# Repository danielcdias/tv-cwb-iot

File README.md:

# tv-cwb-iot

Projeto de pesquisa **Terraço Verde Curitiba IoT**. Rede de sensores criada para monitorar protótipo de telhado verde, efetuando comparação entre tipo de cobertura intensiva e extensiva. Coleta de dados sobre temperatura do solo, quantidade de chuva, atraso de pico e água absorvida.

Este projeto implementa o firmware dos microcontroladores ligados aos sensores, o border router que liga a rede de sensores à internet, e do servidor de aplicação que recebe dos dados coletados, os trata e dispobibiliza através de aplicação web e móvel.

As pastas do projeto estão organizadas da seguinte forma:
- *contiki*: sistema operacional contiki, contendo o código para criação do firmware dos microcontroladores responsáveis pela leitura dos sensores.
- *docker*: configuração para executar o servidor de aplicação (Django/Python) e o banco de dados (MariaDB) em um docker composer.
- *forwarder*: aplicação em Python responsável por receber os dados dos microcontroladores e encaminhá-los ao servidor de aplicação.
- *mobile*: aplicação móvel desenvolvida em Google Flutter para apresentar os dados lidos dos sensores (ainda não implementado).
- *pcb*: projeto de placas impressas utilizadas no projeto.
- *server*: servidor de aplicação desenvolvido em Django/Python, responsável por receber, tratar, armazenar e apresentar os dados lidos pela rede de sensores.

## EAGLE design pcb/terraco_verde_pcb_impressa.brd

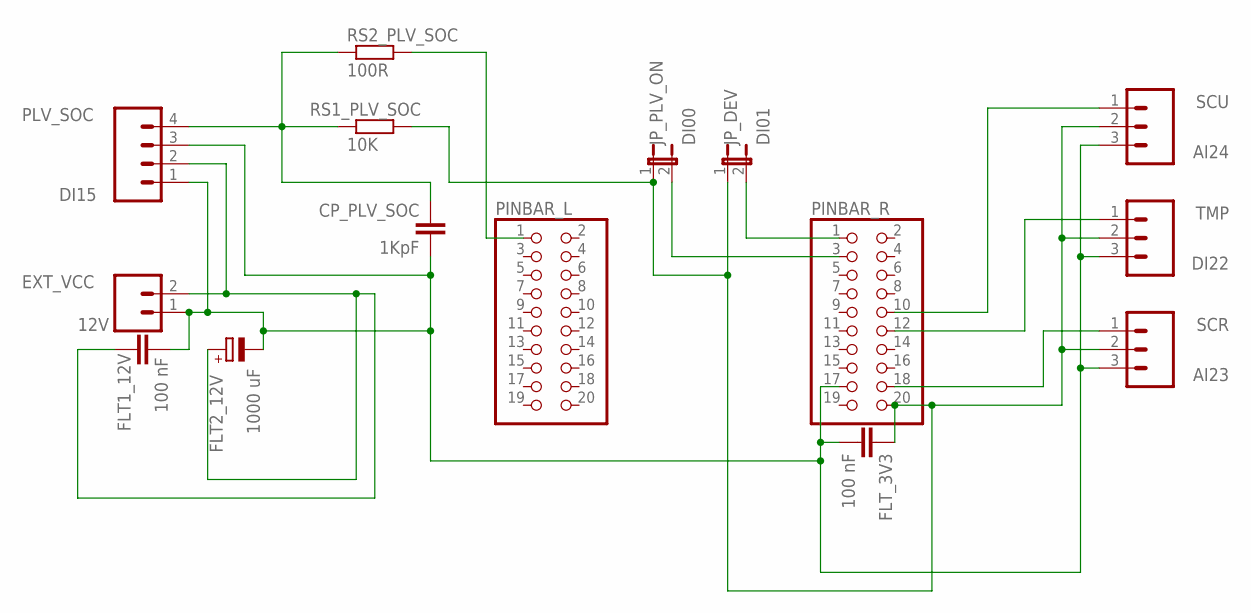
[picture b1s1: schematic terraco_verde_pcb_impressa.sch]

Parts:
CP_PLV_SOC: 1KpF; C025-024X044
EXT_VCC: 12V; 02P
FLT1_12V: 100 nF; C025-024X044
FLT2_12V: 1000 uF; E5-5
FLT_3V3: 100 nF; C025-024X044
JP_DEV: DI01; JP1
JP_PLV_ON: DI00; JP1
PINBAR_L: 0; 2X10
PINBAR_R: 1; 2X10
PLV_SOC: DI15; 04P
RS1_PLV_SOC: 10K; 0207/7
RS2_PLV_SOC: 100R; 0207/7
SCR: AI23; 03P
SCU: AI24; 03P
TMP: DI22; 03P

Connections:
GND: CP_PLV_SOC.1, EXT_VCC.1, FLT1_12V.2, FLT2_12V.-, FLT_3V3.2, PINBAR_R.17, PLV_SOC.1, PLV_SOC.3, SCR.3, SCU.3, TMP.3
NAI23: PINBAR_R.18, SCR.1
NAI24: PINBAR_R.10, SCU.1
NDI00: JP_PLV_ON.2, PINBAR_R.3
NDI01: JP_DEV.2, PINBAR_R.1
NDI15: PINBAR_L.1, RS2_PLV_SOC.2
NDI15_2: CP_PLV_SOC.2, PLV_SOC.4, RS1_PLV_SOC.1, RS2_PLV_SOC.1
NDI22: PINBAR_R.12, TMP.1
VCC_3V3: FLT_3V3.1, JP_DEV.1, JP_PLV_ON.1, PINBAR_R.20, RS1_PLV_SOC.2, SCR.2, SCU.2, TMP.2
VCC_12V: EXT_VCC.2, FLT1_12V.1, FLT2_12V.+, PLV_SOC.2

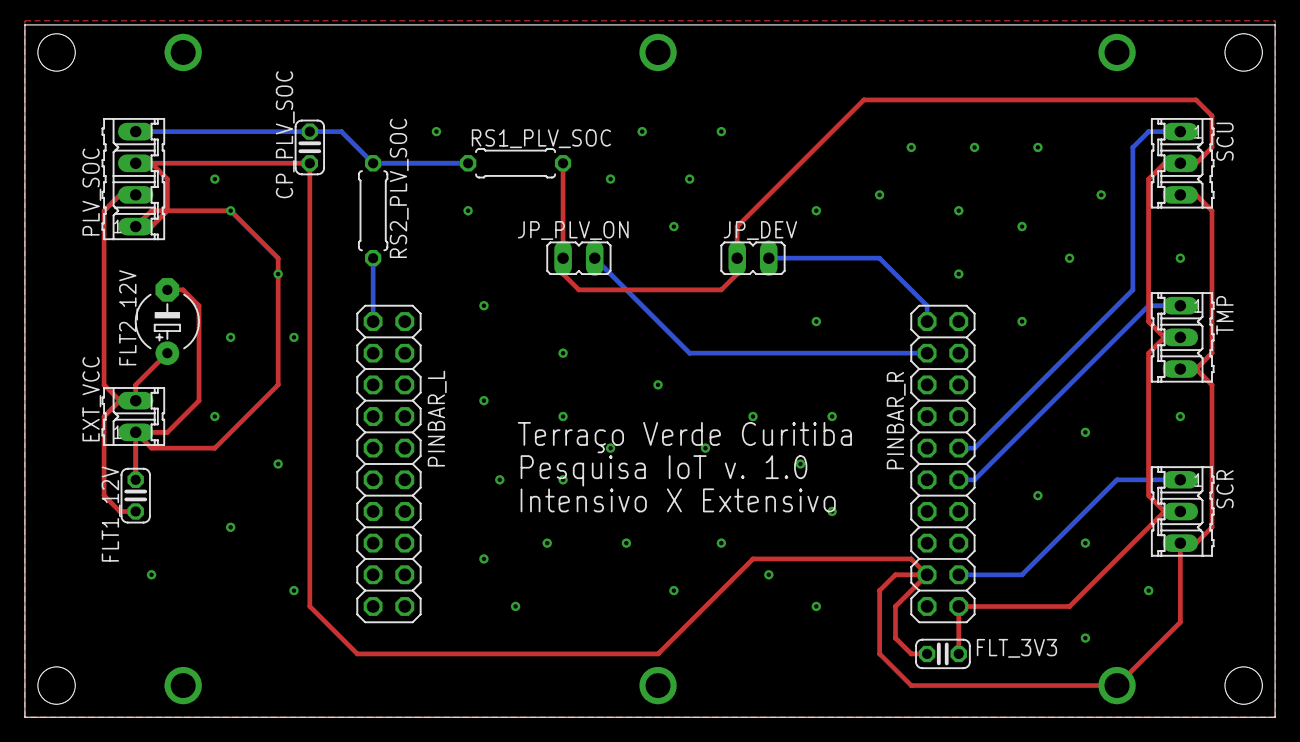
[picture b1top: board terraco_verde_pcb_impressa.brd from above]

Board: 2 copper layers, 100.3 x 55.6 mm, 15 parts (0 on the bottom side), 10 nets.

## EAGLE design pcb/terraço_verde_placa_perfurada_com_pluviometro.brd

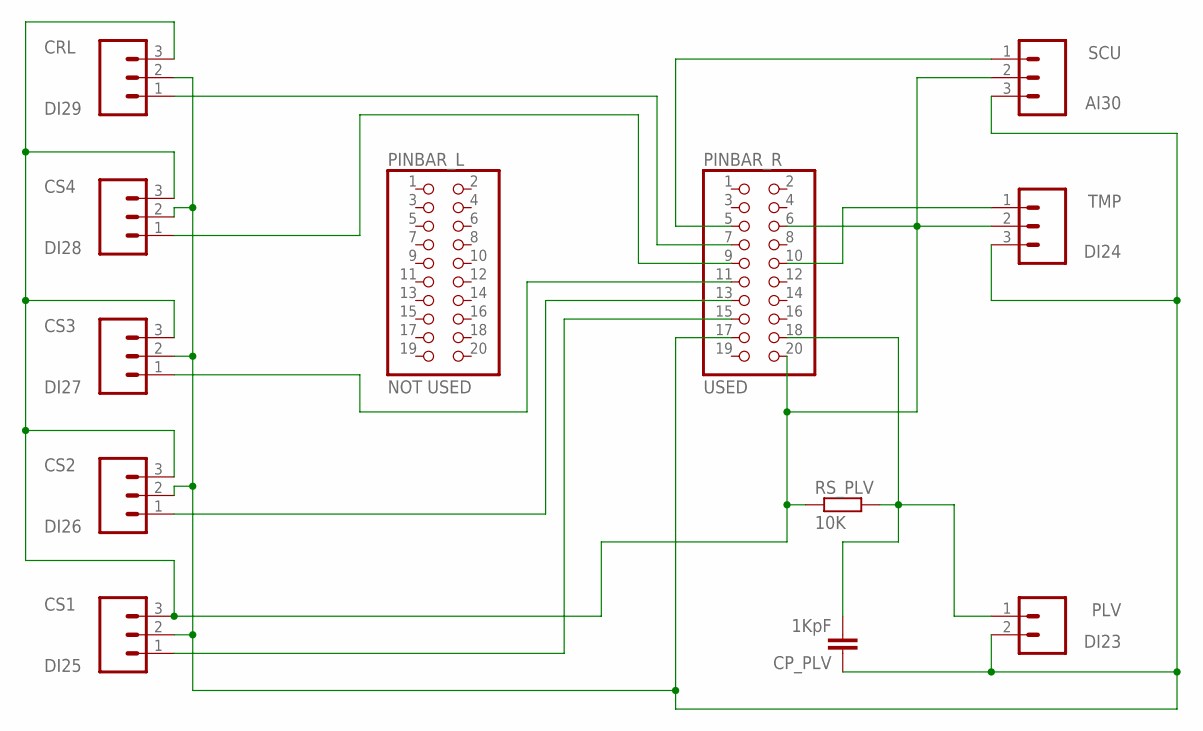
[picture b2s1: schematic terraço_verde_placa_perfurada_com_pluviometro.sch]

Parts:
CP_PLV: 1KpF; C025-024X044
CRL: DI29; 03P
CS1: DI25; 03P
CS2: DI26; 03P
CS3: DI27; 03P
CS4: DI28; 03P
PINBAR_L: NOT USED; 2X10
PINBAR_R: USED; 2X10
PLV: DI23; 02P
RS_PLV: 10K; 0207/7
SCU: AI30; 03P
TMP: DI24; 03P

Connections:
unnamed: PINBAR_R.5, SCU.1
unnamed: CRL.1, PINBAR_R.7
unnamed: CS4.1, PINBAR_R.9
unnamed: CS3.1, PINBAR_R.11
unnamed: CS2.1, PINBAR_R.13
unnamed: CS1.1, PINBAR_R.15
unnamed: PINBAR_R.10, TMP.1
unnamed: CP_PLV.2, PINBAR_R.18, PLV.1, RS_PLV.2
unnamed: CP_PLV.1, CRL.2, CS1.2, CS2.2, CS3.2, CS4.2, PINBAR_R.17, PLV.2, SCU.3, TMP.3
unnamed: CRL.3, CS1.3, CS2.3, CS3.3, CS4.3, PINBAR_R.6, PINBAR_R.20, RS_PLV.1, SCU.2, TMP.2

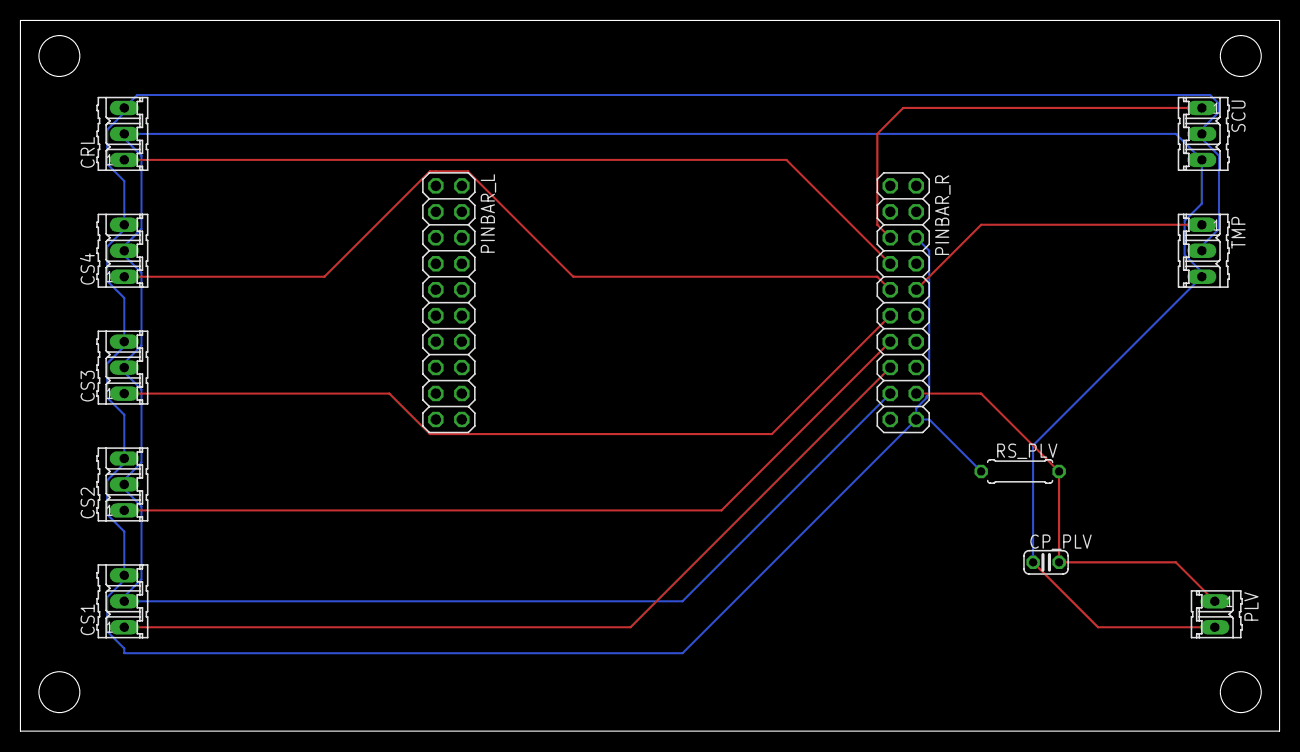
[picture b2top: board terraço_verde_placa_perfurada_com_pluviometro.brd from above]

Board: 2 copper layers, 123.2 x 69.5 mm, 12 parts (0 on the bottom side), 10 nets.

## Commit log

2019-11-19 Atualização do README.md.
2019-11-19 Inclusão do submódulo contiki, ligado ao projeto tv-cwb-iot-contiki.
2019-11-19 Incluindo demais módulos do projeto.
2019-11-23 Inclusão da pasta 'pcb' contendo os projetos das PCBs utilizadas no projeto.
2019-11-26 Alteração no projeto da PCB para incluir plano de terra e vias.
2019-12-05 Bump django from 2.2.5 to 2.2.8 in /server
    Bumps [django](https://github.com/django/django) from 2.2.5 to 2.2.8.
    - [Release notes](https://github.com/django/django/releases)
    - [Commits](https://github.com/django/django/compare/2.2.5...2.2.8)
2020-01-23 Atualização para Python 3.8.
2020-01-24 Inclusão de valores default para admin na criação do DB.
2020-01-24 Inclusão de script SQL para extração de dados do MySQL.
2020-01-30 Melhoria na query SQL de exporte de dados de lidos dos sensores.
2020-02-06 Inclusão de tabela de estado atual das controladoras no HTML de boards.
2020-02-07 Incluindo último pedido de atualização de data e hora na tabela de estado das controladoras.
2020-02-09 Inclusão do motivo do reset das controladoras e contadores de reset e TUR.
2020-02-11 Bump django from 3.0.2 to 3.0.3 in /server
    Bumps [django](https://github.com/django/django) from 3.0.2 to 3.0.3.
    - [Release notes](https://github.com/django/django/releases)
    - [Commits](https://github.com/django/django/compare/3.0.2...3.0.3)
2020-02-11 Atualização para Django 3.0.3 (aviso do dependabot) e correção do cálculo de data para usar timestamp com fuso horário.
2020-02-29 Alteração no processo de extração e cálculo de dados de atraso de pico e quantidade de chuva.
2020-03-05 Criação dos processos de extração de dados para temperatura e absorção de água.
2020-03-05 Correção na extração de dados do atraso de pico.
2020-03-06 Inclusão de multi seleção de sensores em filtro da página de eventos de sensores.
2020-03-06 Inclusão de seletor de data e hora nos filtros.
2020-03-10 Criação de página inicial que mostra dados disponíveis da pesquisa por tipo de informação. Inicialmente, somente temperatura está disponível.
2020-03-11 Correções e melhorias na página de dados de temperatura.
2020-03-12 Correção nos intervalos máximo e mínimo do eixo Y para o gráfico de temperatura.
2020-03-12 Inclusão de média mensal no gráfico de temperatura.
2020-03-13 Melhorias e novas validações para gráfico de temperatura.
2020-03-13 Correções no gráfico de temperatura.
2020-03-14 Correções no gráfico de temperatura e na tela inicial.
2020-05-28 Inclusão do gráfico de absorção de água nos modelos.
2020-06-06 Bump django from 3.0.4 to 3.0.7 in /server
    Bumps [django](https://github.com/django/django) from 3.0.4 to 3.0.7.
    - [Release notes](https://github.com/django/django/releases)
    - [Commits](https://github.com/django/django/compare/3.0.4...3.0.7)
2021-03-18 Bump django from 3.0.4 to 3.1.6 in /server
    Bumps [django](https://github.com/django/django) from 3.0.4 to 3.1.6.
    - [Release notes](https://github.com/django/django/releases)
    - [Commits](https://github.com/django/django/compare/3.0.4...3.1.6)
2021-03-19 Bump djangorestframework from 3.11.0 to 3.11.2 in /server
    Bumps [djangorestframework](https://github.com/encode/django-rest-framework) from 3.11.0 to 3.11.2.
    - [Release notes](https://github.com/encode/django-rest-framework/releases)
    - [Commits](https://github.com/encode/django-rest-framework/compare/3.11.0...3.11.2)
2021-03-30 Bump django from 3.0.4 to 3.0.12 in /server
    Bumps [django](https://github.com/django/django) from 3.0.4 to 3.0.12.
    - [Release notes](https://github.com/django/django/releases)
    - [Commits](https://github.com/django/django/compare/3.0.4...3.0.12)
2021-04-08 Bump django from 3.0.4 to 3.0.14 in /server
    Bumps [django](https://github.com/django/django) from 3.0.4 to 3.0.14.
    - [Release notes](https://github.com/django/django/releases)
    - [Commits](https://github.com/django/django/compare/3.0.4...3.0.14)
2021-06-02 Bump urllib3 from 1.25.8 to 1.26.5 in /forwarder
    Bumps [urllib3](https://github.com/urllib3/urllib3) from 1.25.8 to 1.26.5.
    - [Release notes](https://github.com/urllib3/urllib3/releases)
    - [Changelog](https://github.com/urllib3/urllib3/blob/main/CHANGES.rst)
    - [Commits](https://github.com/urllib3/urllib3/compare/1.25.8...1.26.5)
    ---
    updated-dependencies:
2021-06-04 Bump django from 3.0.4 to 3.1.9 in /server
    Bumps [django](https://github.com/django/django) from 3.0.4 to 3.1.9.
    - [Release notes](https://github.com/django/django/releases)
    - [Commits](https://github.com/django/django/compare/3.0.4...3.1.9)
    ---
    updated-dependencies:
    - dependency-name: django
2021-06-10 Bump django from 3.0.4 to 3.1.12 in /server
    Bumps [django](https://github.com/django/django) from 3.0.4 to 3.1.12.
    - [Release notes](https://github.com/django/django/releases)
    - [Commits](https://github.com/django/django/compare/3.0.4...3.1.12)
    ---
    updated-dependencies:
    - dependency-name: django
2021-09-22 Bump django from 3.0.4 to 3.1.13 in /server
    Bumps [django](https://github.com/django/django) from 3.0.4 to 3.1.13.
    - [Release notes](https://github.com/django/django/releases)
    - [Commits](https://github.com/django/django/compare/3.0.4...3.1.13)
    ---
    updated-dependencies:
    - dependency-name: django
2022-12-08 Bump certifi from 2019.11.28 to 2022.12.7 in /forwarder
    Bumps [certifi](https://github.com/certifi/python-certifi) from 2019.11.28 to 2022.12.7.
    - [Release notes](https://github.com/certifi/python-certifi/releases)
    - [Commits](https://github.com/certifi/python-certifi/compare/2019.11.28...2022.12.07)
    ---
    updated-dependencies:
    - dependency-name: certifi
